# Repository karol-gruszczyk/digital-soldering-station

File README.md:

# Digital soldering station  
Integrated soldering/hot-air station, variable voltage/current power supply

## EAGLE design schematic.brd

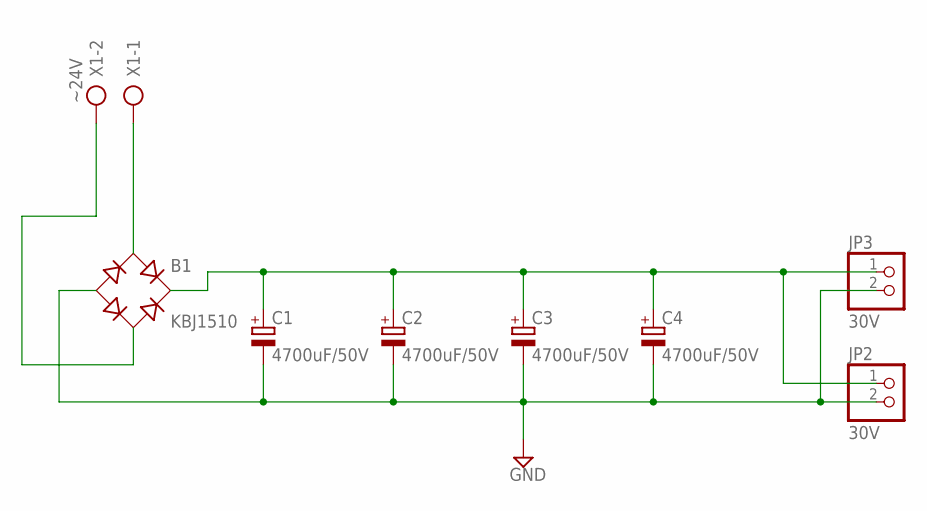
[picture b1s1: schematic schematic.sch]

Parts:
B1: KBJ1510; FB32
C1, C2, C3, C4: 4700uF/50V; EB20D
JP2, JP3: 30V; 1X02
X1: ~24V; AK500/2

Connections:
GND: B1.-, C1.-, C2.-, C3.-, C4.-, JP2.2, JP3.2
unnamed: B1.AC2, X1.2
unnamed: B1.AC1, X1.1
unnamed: B1.+, C1.+, C2.+, C3.+, C4.+, JP2.1, JP3.1

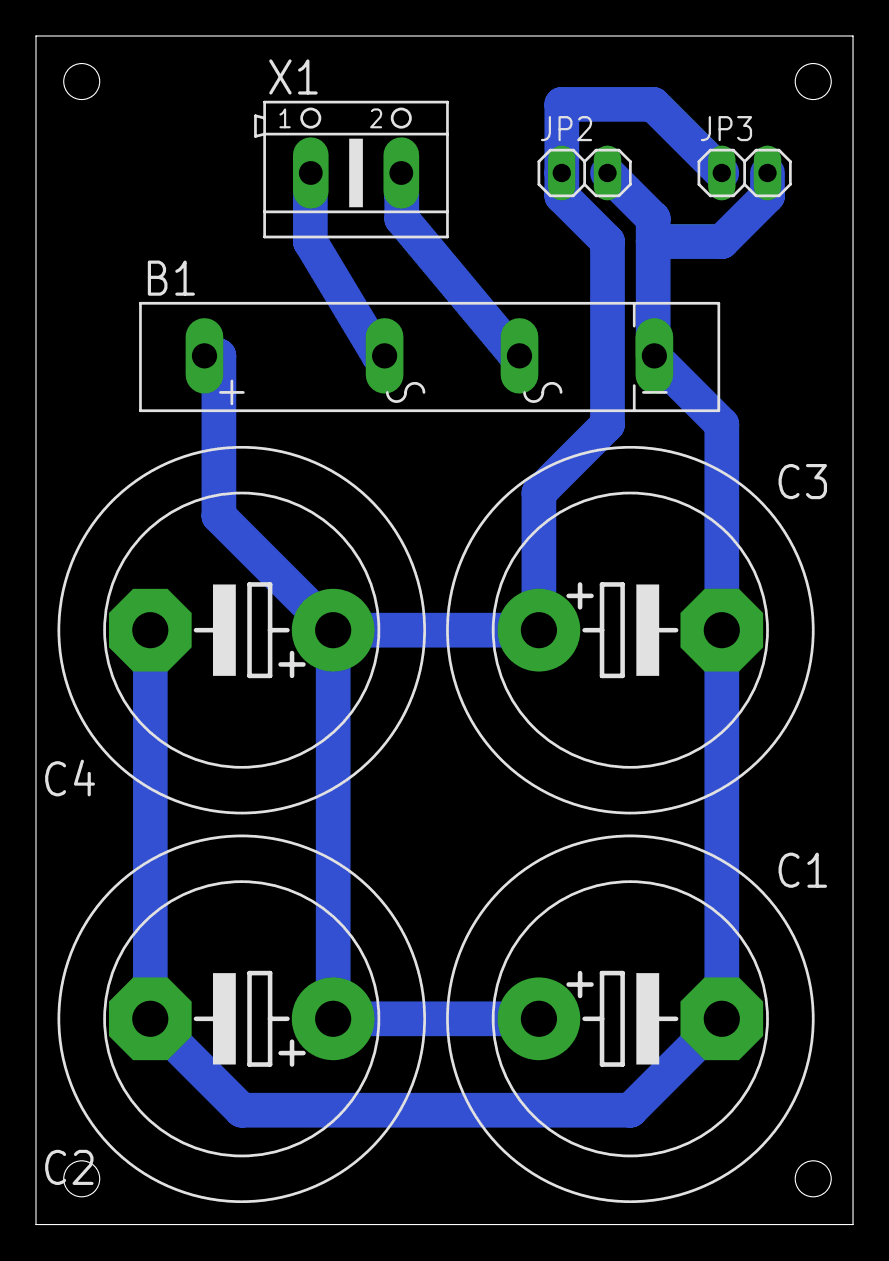
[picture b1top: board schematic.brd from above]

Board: 2 copper layers, 45.4 x 66.0 mm, 8 parts (0 on the bottom side), 4 nets.

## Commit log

2016-09-20 added readme
2016-09-24 added multi func button handling
2017-01-31 added power supply circuit schematic
2017-01-31 added desc to readme
2017-02-04 added LCD support
2017-02-07 added power supply board
2017-02-07 added holes to power supply board
2017-02-21 added schematics and iron controller logic
